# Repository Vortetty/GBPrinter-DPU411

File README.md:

# DPU411-Based gameboy printer replacement

Uses a clone of the Gameboy Printer emulator to act as a printer, while managing a thermal printer to print at a larger size.

This version is made for the DPU411 Type 2 printer, schematics are in the DRIVER folder and require kicad, the pcb is not guaranteed to work as i have not been able to try it.

The code here shold be adaptable to virtually every thermal printer you find, maybe even some non-thermal if you write enough code. All you need to change is the head control and init code to match your printer, the decoding can be the same in 99% of cases.

## How to set up

1. Build the printer as shown in the schematic, will require pulling all the boards out and replacing them with alot of wiring.
2. Flash the micro with the code found in [this repo](https://github.com/Vortetty/arduino-gameboy-printer-parser-for-DPU411TYPE2-printer)
3. Flash the pico with the code found here
4. Connect to a GB/GBA and enjoy!

## Example

")

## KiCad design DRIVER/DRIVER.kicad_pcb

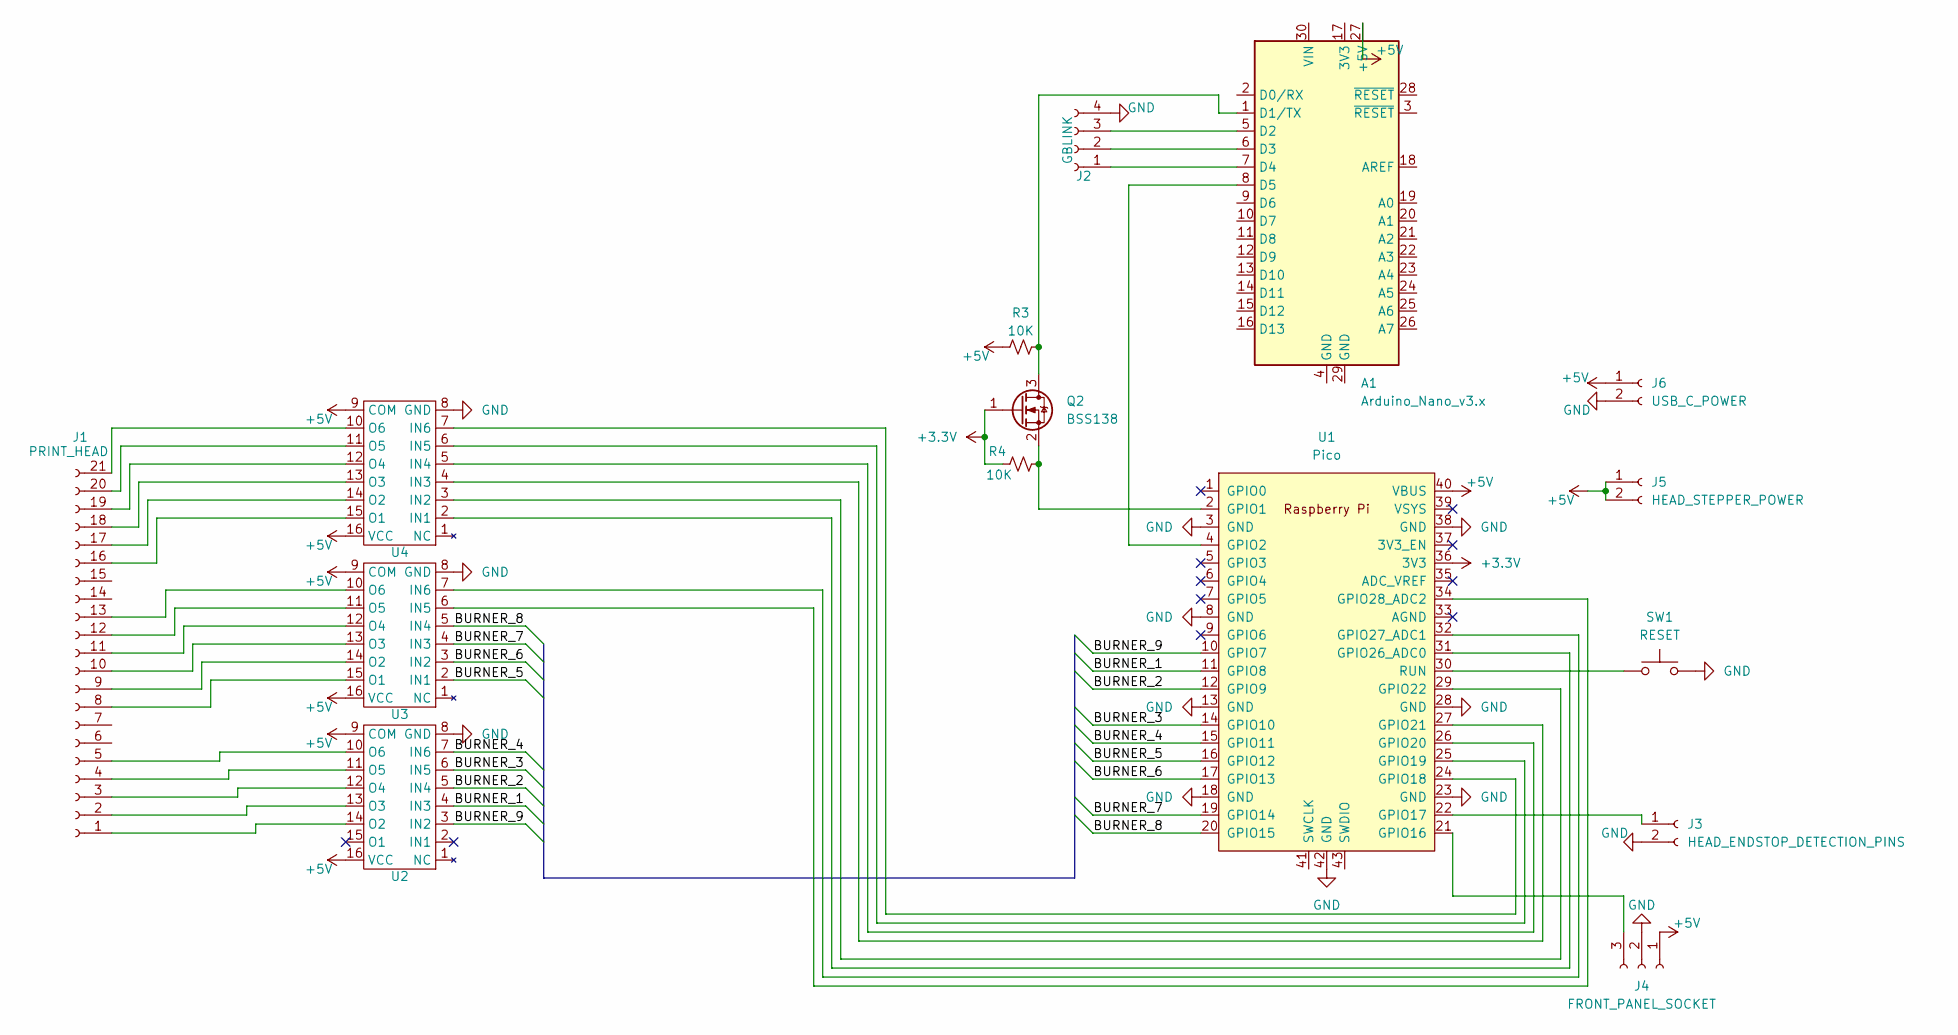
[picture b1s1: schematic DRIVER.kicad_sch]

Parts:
A1: Arduino_Nano_v3.x; Arduino_Nano
J1: PRINT_HEAD; PinHeader_1x21_P2.54mm_Vertical
J2: GBLINK; PinHeader_1x03_P2.54mm_Vertical
J3: HEAD_ENDSTOP_DETECTION_PINS; PinHeader_1x02_P2.54mm_Vertical
J4: FRONT_PANEL_SOCKET; PinHeader_1x03_P2.54mm_Vertical
J5: HEAD_STEPPER_POWER; PinHeader_1x02_P2.54mm_Vertical
J6: USB_C_POWER; PinHeader_1x02_P1.00mm_Vertical
Q2: BSS138; SOT-23
R3, R4: 10K; R_0201_0603Metric_Pad0.64x0.40mm_HandSolder
SW1: RESET; SW_Push_1P1T_NO_Vertical_Wuerth_434133025816
U1: Pico; RPi_Pico_SMD_TH
U2, U3, U4: DIP-16_W7.62mm_Socket

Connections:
+3.3V: Q2.1 (G), R4.2, U1.36 (3V3)
+5V: A1.27 (+5V), J4.1, J5.1, J5.2, J6.1, R3.1, U1.40 (VBUS), U2.9 (COM), U2.16 (VCC), U3.9 (COM), U3.16 (VCC), U4.9 (COM), U4.16 (VCC)
/BURNER_1: U1.11 (GPIO8), U2.4 (IN3)
/BURNER_2: U1.12 (GPIO9), U2.5 (IN4)
/BURNER_3: U1.14 (GPIO10), U2.6 (IN5)
/BURNER_4: U1.15 (GPIO11), U2.7 (IN6)
/BURNER_5: U1.16 (GPIO12), U3.2 (IN1)
/BURNER_6: U1.17 (GPIO13), U3.3 (IN2)
/BURNER_7: U1.19 (GPIO14), U3.4 (IN3)
/BURNER_8: U1.20 (GPIO15), U3.5 (IN4)
/BURNER_9: U1.10 (GPIO7), U2.3 (IN2)
GND: J2.4, J3.2, J4.2, J6.2, SW1.2, U1.3 (GND), U1.8 (GND), U1.13 (GND), U1.18 (GND), U1.23 (GND), U1.28 (GND), U1.38 (GND), U1.42 (GND), U2.8 (GND), U3.8 (GND), U4.8 (GND)
unnamed: A1.1 (D1/TX), Q2.3 (D), R3.2
unnamed: A1.5 (D2), J2.3
unnamed: A1.6 (D3), J2.2
unnamed: A1.7 (D4), J2.1
unnamed: A1.8 (D5), U1.4 (GPIO2)
unnamed: J1.1, U2.14 (O2)
unnamed: J1.2, U2.13 (O3)
unnamed: J1.3, U2.12 (O4)
unnamed: J1.4, U2.11 (O5)
unnamed: J1.5, U2.10 (O6)
unnamed: J1.8, U3.15 (O1)
unnamed: J1.9, U3.14 (O2)
unnamed: J1.10, U3.13 (O3)
unnamed: J1.11, U3.12 (O4)
unnamed: J1.12, U3.11 (O5)
unnamed: J1.13, U3.10 (O6)
unnamed: J1.16, U4.15 (O1)
unnamed: J1.17, U4.14 (O2)
unnamed: J1.18, U4.13 (O3)
unnamed: J1.19, U4.12 (O4)
unnamed: J1.20, U4.11 (O5)
unnamed: J1.21, U4.10 (O6)
unnamed: J3.1, U1.22 (GPIO17)
unnamed: J4.3, U1.21 (GPIO16)
unnamed: Q2.2 (S), R4.1, U1.2 (GPIO1)
unnamed: U1.24 (GPIO18), U4.7 (IN6)
unnamed: U1.25 (GPIO19), U4.6 (IN5)
unnamed: U1.26 (GPIO20), U4.5 (IN4)
unnamed: U1.27 (GPIO21), U4.4 (IN3)
unnamed: U1.29 (GPIO22), U4.3 (IN2)
unnamed: U1.31 (GPIO26_ADC0), U4.2 (IN1)
unnamed: U1.32 (GPIO27_ADC1), U3.7 (IN6)
unnamed: U1.34 (GPIO28_ADC2), U3.6 (IN5)
unnamed: SW1.1, U1.30 (RUN)

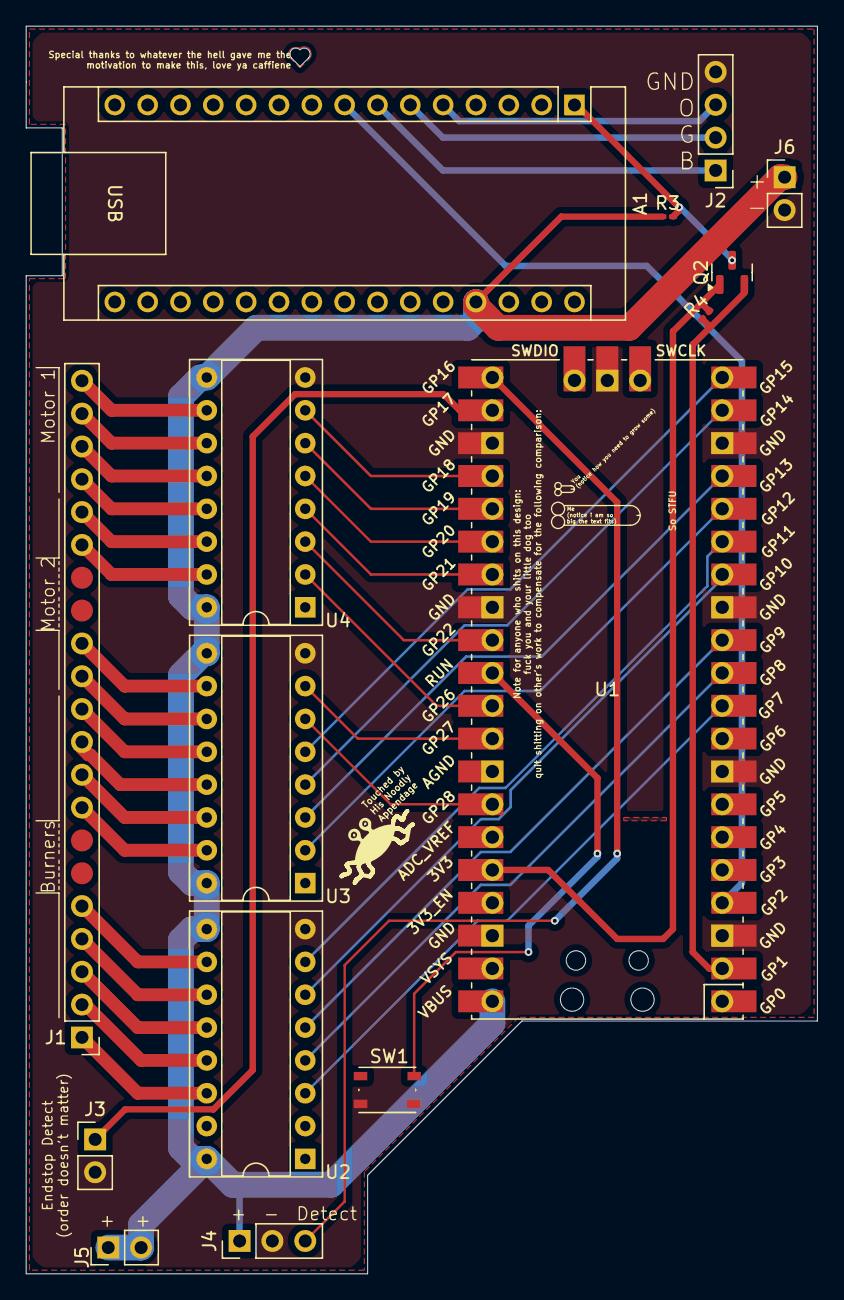
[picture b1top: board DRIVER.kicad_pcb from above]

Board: 2 copper layers, 61.2 x 96.5 mm, 15 parts (0 on the bottom side), 46 nets.

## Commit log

2024-12-08 Initial commit because i forgot to version control this
2024-12-08 Update README.md
    Add extra info
2024-12-08 Create LICENSE
